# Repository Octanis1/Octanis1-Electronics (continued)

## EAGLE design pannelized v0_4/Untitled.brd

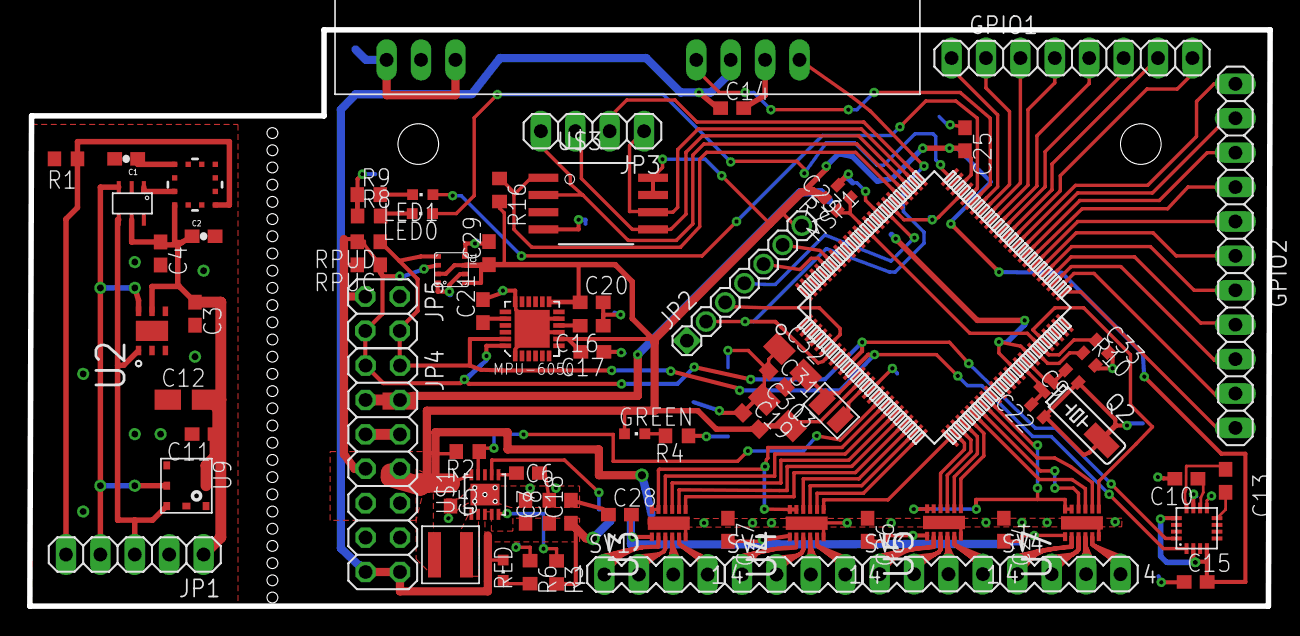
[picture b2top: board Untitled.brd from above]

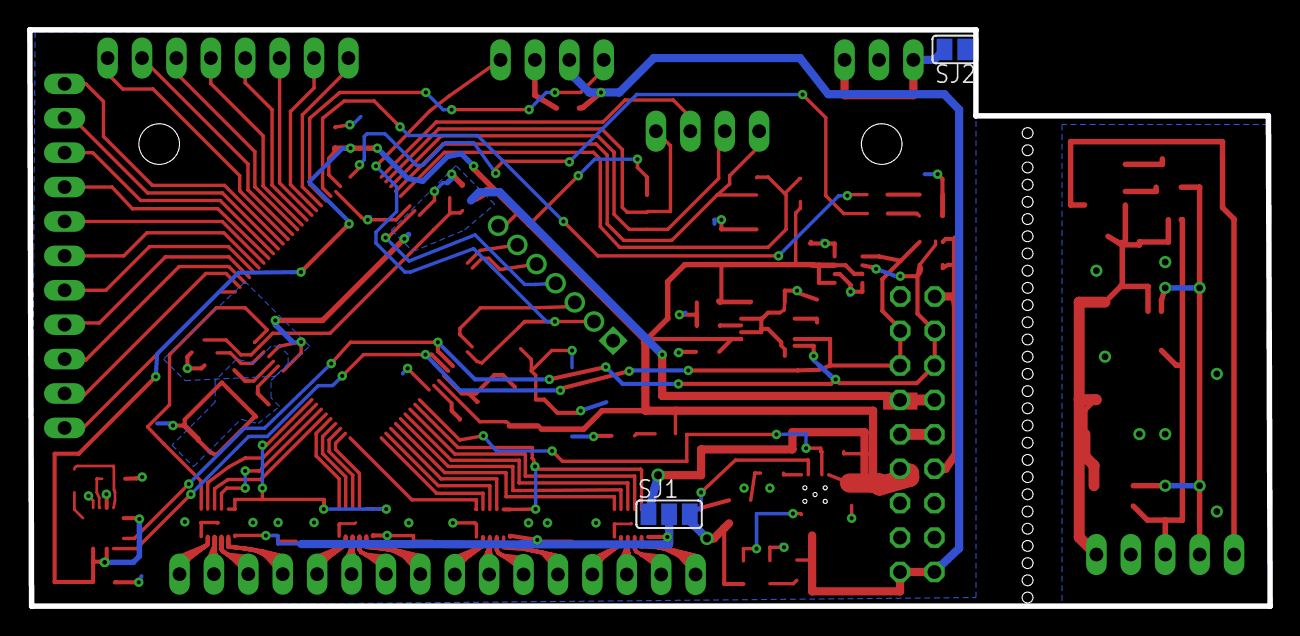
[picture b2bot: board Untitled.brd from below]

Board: 2 copper layers, 91.6 x 42.5 mm, 81 parts (2 on the bottom side), 100 nets.

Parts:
C1: 1nF; 0603-CAP
C2: 0.1uF; 0603-CAP
C3, C4, C11, C14, C15, C16, C19, C20, C25, C29, C31: 100n; C0603
C5, C7, C8: 22uF; C0603
C6: 10nF; C0603
C9, C22: 12p; C0402
C10: 4.7u; C0603
C12, C30, C32: 10u; A/3216-18R
C13: 220n; C0603
C17: 10n; C0603
C18: 3 x 22uF; C0603
C21: 2.2n; C0603
C23, C33: 100n; C0402
C24, C26, C27, C28: 470n; C0603
COMPASS: HMC5883L; LPCC16
GPIO1: A7:A0; 1X08
GPIO2: A18:A8; 1X11
GREEN: 3V-ok; CHIPLED_0603
IC1: BME280
JP1: 1X05
JP2: 1:07X2MM
JP3: SPI; 1X04
JP4: 2X07
JP5: 2X02
L1: 1uH; XFL4020
L3: 4.7uH; 0806
LED0: LED0; CHIPLED_0603
LED1: LED1; CHIPLED_0603
MPU-6050: MPU-6050; QFN24
MSP1: MSP432; PZ100
Q2: 32.768kHz; MS3V-T1R
R1, R16: 10k; R0603
R2, R3: 1M; R0603
R4, R6, R8, R9: 1k; R0603
R7: 0R; R0402
R10: 91k 0.1% ±25 ppm/°C; R0402
RED: 5V-ok; CHIPLED_0603
RPUC: 10k; R0603
RPUD: 10k; R0603
SJ1: 3V3 V_Motor 5V; SJ_2
SJ2: SJ
SV1, SV2, SV3, SV4: MA04-1
U1: ML8511-UV-SENSOR; ML8511
U2: SHT21; DFN300X300X110-7N
U3, U4, U5, U7: DRV8836DSSR; SON50P200X300X80-13N
U9: BMP180
U$1: TPS61232; S-PVSON-N10
U$2: STARGND; STAR
U$3: SST25VF064C; SOIC_8-LEAD
U$4: HX1
U$5: MCP3425; SOT-23-6

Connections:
5VEN: MSP1.17, R2.1, U$1.9
+3V1: C5.1, C15.2, C17.2, C19.2, C20.1, C25.2, C29.1, C30.+, COMPASS.2, COMPASS.4, COMPASS.13, GREEN.A, IC1.2, IC1.6, IC1.8, JP2.7, JP4.7, JP4.8, JP4.9, JP4.10, JP5.1, L1.P$1, MPU-6050.8, MPU-6050.13, MSP1.13, MSP1.73, R2.2, R7.2, R16.2, RPUC.2, RPUD.2, SJ1.1, U$1.10, U$3.RST/HOLD, U$3.VDD
+3V3: C2.1, C3.1, C4.1, C11.1, C12.+, JP1.1, U1.7, U2.5, U9.2, U9.3, U$5.VDD
+5V: C7.1, C8.1, C14.1, C18.1, JP4.13, JP4.14, R3.2, RED.A, SJ1.3, U$1.3, U$1.4, U$1.7, U$4.VCC
A14: GPIO2.7, MSP1.55
A15: GPIO2.8, MSP1.54
A16: GPIO2.9, MSP1.53
A17: GPIO2.10, MSP1.52
A18: GPIO2.11, MSP1.51
AGND: C23.2, C33.2, MSP1.40, MSP1.43, MSP1.84, R10.2, U$2.AGND
AVCC1: C23.1, C33.1, MSP1.45, MSP1.87, R7.1
GND: C1.2, C2.2, C3.2, C4.2, C11.2, C12.-, JP1.2, R1.2, U1.5, U2.2, U9.7, U$5.VIN-, U$5.VSS
GND1: C5.2, C6.2, C7.2, C8.2, C9.1, C10.2, C14.2, C15.1, C16.1, C17.1, C18.2, C19.1, C20.2, C21.2, C22.1, C24.1, C25.1, C26.1, C27.1, C28.1, C29.2, C30.-, C31.1, C32.-, COMPASS.9, COMPASS.11, IC1.1, IC1.5, IC1.7, JP2.1, JP4.3, JP4.4, JP4.5, JP4.6, JP4.11, JP4.12, JP5.2, MPU-6050.1, MPU-6050.9, MPU-6050.11, MPU-6050.18, MPU-6050.P, MSP1.15, MSP1.72, MSP1.82, Q2.P3, R4.1, R6.1, R8.1, R9.1, SJ2.1, U3.6, U3.13, U4.6, U4.13, U5.6, U5.13, U7.6, U7.13, U$1.EXPAD, U$2.DGND, U$2.GND, U$3.VSS, U$4.0V
HX1_EN: MSP1.70, U$4.EN
IND: L1.P$2, U$1.1, U$1.2
LED0: LED0.A, MSP1.75
LED1: LED1.A, MSP1.71
M1IN1: MSP1.19, U3.10
M1IN2: MSP1.20, U3.9
M2IN1: MSP1.21, U3.8
M2IN2: MSP1.22, U3.7
M3IN1: MSP1.23, U4.10
M3IN2: MSP1.24, U4.9
M4IN1: MSP1.25, U4.8
M4IN2: MSP1.26, U4.7
M5IN1: MSP1.27, U5.10
M5IN2: MSP1.28, U5.9
M6IN1: MSP1.29, U5.8
M6IN2: MSP1.30, U5.7
M7IN1: MSP1.32, U7.10
M7IN2: MSP1.31, U7.9
M8IN1: MSP1.33, U7.8
M8IN2: MSP1.46, U7.7
M1234SLEEP: MSP1.18, U3.11, U3.12, U4.11, U4.12
M5678SLEEP: MSP1.34, U5.11, U5.12, U7.11, U7.12
unnamed: U1.8, U$5.VIN+
unnamed: R3.1, U$1.5
unnamed: C1.1, U1.10
unnamed: GREEN.C, R4.2
unnamed: LED0.C, R8.2
unnamed: LED1.C, R9.2
unnamed: C31.2, C32.+, L3.1, MSP1.12
unnamed: C22.2, MSP1.41, Q2.P2
unnamed: C9.2, MSP1.42, Q2.P1
unnamed: SV2.1, U4.2
unnamed: GPIO2.1, MSP1.61
unnamed: GPIO2.2, MSP1.60
unnamed: C10.1, COMPASS.10
unnamed: C16.2, MPU-6050.10
unnamed: C21.1, MPU-6050.20
unnamed: GPIO2.3, MSP1.59
unnamed: GPIO2.4, MSP1.58
unnamed: GPIO2.5, MSP1.57
unnamed: GPIO2.6, MSP1.56
unnamed: C13.2, COMPASS.8
unnamed: GPIO1.1, MSP1.69
unnamed: GPIO1.2, MSP1.68
unnamed: GPIO1.3, MSP1.67
unnamed: C13.1, COMPASS.12
unnamed: MSP1.44, R10.1
unnamed: L3.2, MSP1.14
unnamed: GPIO1.4, MSP1.66
unnamed: GPIO1.5, MSP1.65
unnamed: GPIO1.6, MSP1.64
unnamed: GPIO1.8, MSP1.62
unnamed: SV2.2, U4.3
unnamed: SV2.3, U4.4
unnamed: SV2.4, U4.5
unnamed: C6.1, U$1.6
unnamed: GPIO1.7, MSP1.63
unnamed: R6.2, RED.C
unnamed: SV3.1, U5.2
unnamed: SV3.2, U5.3
unnamed: SV3.3, U5.4
unnamed: SV3.4, U5.5
unnamed: SV1.1, U3.2
unnamed: SV1.2, U3.3
unnamed: SV1.3, U3.4
unnamed: SV1.4, U3.5
unnamed: SV4.1, U7.2
unnamed: SV4.2, U7.3
unnamed: SV4.3, U7.4
unnamed: SV4.4, U7.5
unnamed: JP2.4, MSP1.83
unnamed: JP2.6, MSP1.94
unnamed: JP2.5, MSP1.95
RFGND: SJ2.2, U$4.RFGND, U$4.RFGND2
RX: JP2.2, MSP1.6
SCL: JP1.4, U2.6, U9.5, U$5.SCL
SCL1: COMPASS.1, IC1.4, JP4.2, JP5.4, MPU-6050.23, MSP1.11, RPUD.1
SDA: JP1.3, U2.1, U9.6, U$5.SDA
SDA1: COMPASS.16, IC1.3, JP4.1, JP5.3, MPU-6050.24, MSP1.10, RPUC.1
SPI_EXTSLAVE_TE: JP3.2, MSP1.76
SPI_FLASH_CS: MSP1.80, R16.1, U$3.CE
SPI_MISO: JP3.4, MSP1.79, U$3.SO
SPI_MOSI: JP3.3, MSP1.78, U$3.SI
SPI_SCK: JP3.1, MSP1.77, U$3.SCK
TX: JP2.3, MSP1.7, U$4.TXD
UV_EN: JP1.5, R1.1, U1.4
V_MOTOR: C24.2, C26.2, C27.2, C28.2, SJ1.2, U3.1, U4.1, U5.1, U7.1

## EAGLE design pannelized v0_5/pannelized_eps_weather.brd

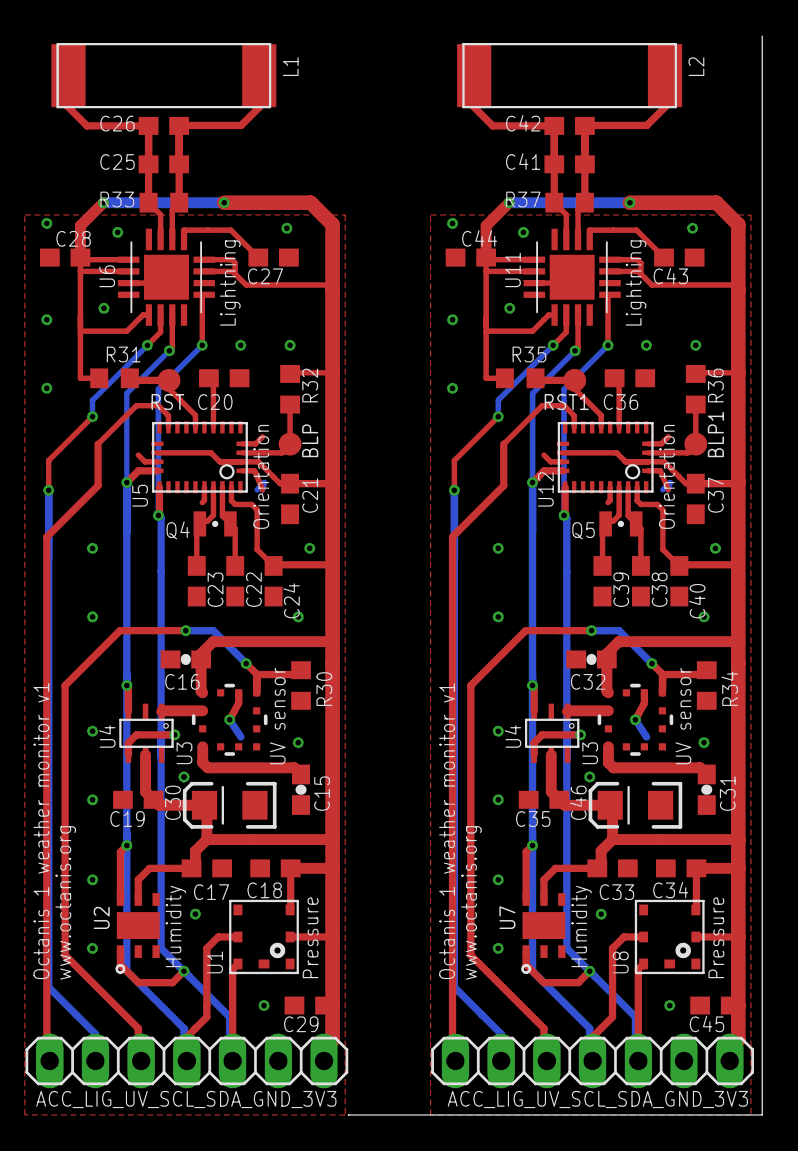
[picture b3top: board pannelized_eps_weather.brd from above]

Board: 4 copper layers, 62 parts (0 on the bottom side), 32 nets.

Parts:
BLP, BLP1: PTR1B1,27; B1,27
C15, C31: 1n; 0603-CAP
C16, C32: 100n; 0603-CAP
C17, C18, C19, C20, C21, C29, C33, C34, C35, C36, C37, C45: 100n; C0603
C22, C23, C38, C39: 12p; C0603
C24, C40: 120n; C0603
C25, C41: 670p; C0603
C26, C42: 270p; C0603
C27, C43: 10u; C0603
C28, C44: 1u; C0603
C30, C46: 10uF; EIA3216
JP4, JP5: 1X07
L1, L2: 100uH; COILCRAFT
Q4, Q5: 32.768kHz; FC-12M
R30, R31, R32, R33, R34, R35, R36, R37: 10k; R0603
RST, RST1: PTR1B1,27; B1,27
U1, U8: BMP180
U2, U7: SHT21; DFN300X300X110-7N
U3, U10: ML8511-UV-SENSORSMD; ML8511
U4, U9: MCP3425; SOT-23-6
U5, U12: BNO055A; BNO055
U6, U11: AS3935; 16LDMLPQ

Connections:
+3V1: C32.1, C33.1, C34.1, C35.1, C37.1, C40.1, C44.2, C45.1, C46.A, JP5.1, R35.1, R36.2, U7.5, U8.2, U8.3, U9.VDD, U10.7, U11.5, U11.6, U11.9, U11.15, U11.16, U12.3, U12.17, U12.28
+3V3: C16.1, C17.1, C18.1, C19.1, C21.1, C24.1, C28.2, C29.1, C30.A, JP4.1, R31.1, R32.2, U1.2, U1.3, U2.5, U3.7, U4.VDD, U5.3, U5.17, U5.28, U6.5, U6.6, U6.9, U6.15, U6.16
ACCEL_IRQ: JP4.7, U5.14
ACCEL_IRQ1: JP5.7, U12.14
ACCEL_N_BOOTLD: BLP.TP, R32.1, U5.4
ACCEL_N_BOOTLD1: BLP1.TP, R36.1, U12.4
ACCEL_N_RST: R31.2, RST.TP, U5.11
ACCEL_N_RST1: R35.2, RST1.TP, U12.11
GND1: C15.2, C16.2, C17.2, C18.2, C19.2, C20.1, C21.2, C22.2, C23.2, C24.2, C25.2, C26.2, C27.1, C28.1, C29.2, C30.C, JP4.2, L1.2, R30.2, R33.1, U1.7, U2.2, U3.5, U4.VIN-, U4.VSS, U5.2, U5.5, U5.6, U5.10, U5.15, U5.16, U5.18, U5.25, U6.2, U6.4, U6.7, U6.EXP
GND2: C31.2, C32.2, C33.2, C34.2, C35.2, C36.1, C37.2, C38.2, C39.2, C40.2, C41.2, C42.2, C43.1, C44.1, C45.2, C46.C, JP5.2, L2.2, R34.2, R37.1, U7.2, U8.7, U9.VIN-, U9.VSS, U10.5, U11.2, U11.4, U11.7, U11.EXP, U12.2, U12.5, U12.6, U12.10, U12.15, U12.16, U12.18, U12.25
LIGHTNING_IRQ: JP4.6, U6.10
LIGHTNING_IRQ1: JP5.6, U11.10
unnamed: C15.1, U3.10
unnamed: U3.8, U4.VIN+
unnamed: C25.1, C26.1, L1.1, R33.2, U6.3
unnamed: C27.2, U6.1
unnamed: C20.2, U5.9
unnamed: C22.1, Q4.2, U5.27
unnamed: C31.1, U10.10
unnamed: U9.VIN+, U10.8
unnamed: C41.1, C42.1, L2.1, R37.2, U11.3
unnamed: C43.2, U11.1
unnamed: C36.2, U12.9
unnamed: C39.1, Q5.1, U12.26
unnamed: C38.1, Q5.2, U12.27
unnamed: C23.1, Q4.1, U5.26
SCL: JP4.4, U1.5, U2.6, U4.SCL, U5.19, U6.11
SCL1: JP5.4, U7.6, U8.5, U9.SCL, U11.11, U12.19
SDA: JP4.3, U1.6, U2.1, U4.SDA, U5.20, U6.13
SDA1: JP5.3, U7.1, U8.6, U9.SDA, U11.13, U12.20
UV_EN: JP4.5, R30.1, U3.4
UV_EN1: JP5.5, R34.1, U10.4

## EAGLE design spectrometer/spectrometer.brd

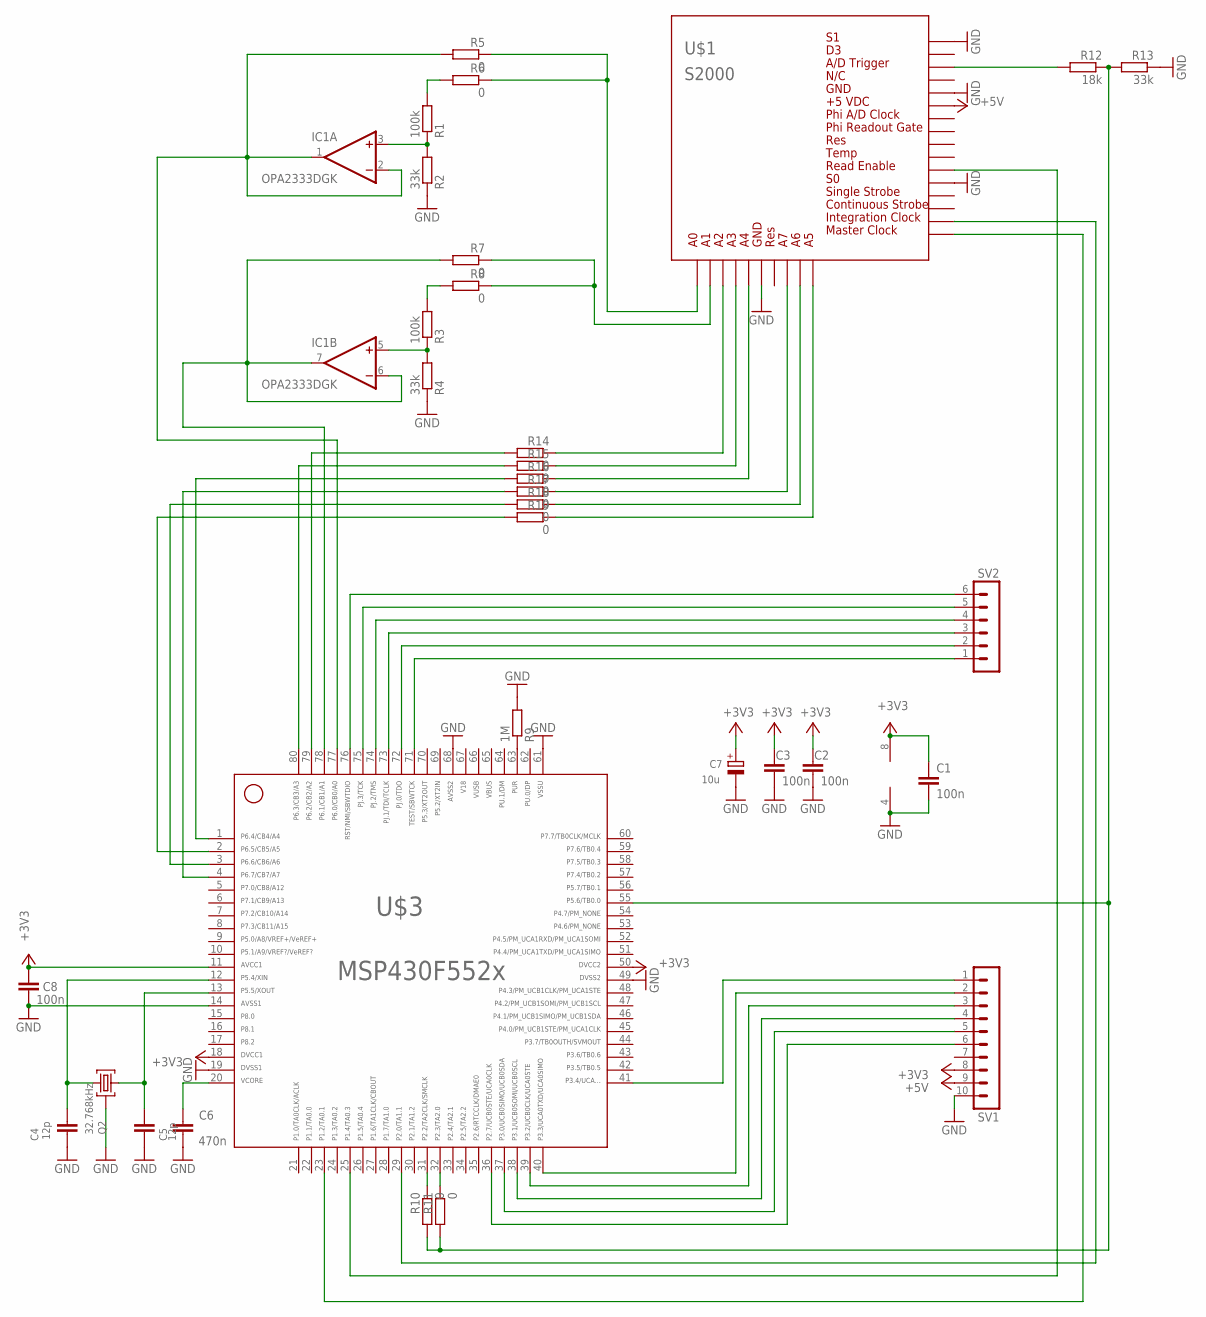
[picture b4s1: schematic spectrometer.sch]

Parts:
C1, C2, C3, C8: 100n; C0603
C4, C5: 12p; C0603
C6: 470n; C0603
C7: 10u; A/3216-18R
IC1: OPA2333DGK; MSOP08
Q2: 32.768kHz; MS3V-T1R
R1, R3: 100k; R0603
R2, R4, R13: 33k; R0603
R5, R6, R7, R8, R10, R11, R14, R15, R16, R17, R18, R19: 0; R0603
R9: 1M; R0603
R12: 18k; R0603
SV1: MA10-1
SV2: MA06-1
U$1: S2000
U$3: F552X---PN80; PN80

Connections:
65: U$3.65
66: U$3.66
67: U$3.67
+3V3: C1.1, C2.2, C3.2, C7.+, C8.1, IC1.8 (V+), SV1.8, U$3.11, U$3.18, U$3.50
+5V: SV1.9, U$1.H2$2
GND: C1.2, C2.1, C3.1, C4.1, C5.1, C6.1, C7.-, C8.2, IC1.4 (V-), Q2.P3 (GND), R2.1, R4.1, R9.2, R13.1, SV1.10, U$1.H1$6, U$1.H2$1, U$1.H2$8, U$1.H2$A, U$3.14, U$3.19, U$3.49, U$3.61, U$3.68
unnamed: IC1.3 (+IN), R1.1, R2.2
unnamed: IC1.5 (+IN), R3.1, R4.2
unnamed: IC1.1 (OUT), IC1.2 (-IN), R5.2, U$3.77
unnamed: IC1.6 (-IN), IC1.7 (OUT), R7.2, U$3.78
unnamed: R1.2, R6.2
unnamed: R3.2, R8.2
unnamed: R5.1, R6.1, U$1.H1$1
unnamed: R7.1, R8.1, U$1.H1$2
unnamed: SV1.1, U$3.41
unnamed: SV1.2, U$3.40
unnamed: SV1.3, U$3.39
unnamed: SV1.4, U$3.38
unnamed: SV1.5, U$3.37
unnamed: SV1.6, U$3.36
unnamed: R14.2, U$3.79
unnamed: R15.2, U$3.80
unnamed: R16.2, U$3.1
unnamed: R17.2, U$3.4
unnamed: R18.2, U$3.3
unnamed: R19.2, U$3.2
unnamed: R9.1, U$3.63
unnamed: SV2.1, U$3.71
unnamed: SV2.2, U$3.72
unnamed: SV2.3, U$3.73
unnamed: SV2.4, U$3.74
unnamed: SV2.5, U$3.75
unnamed: SV2.6, U$3.76
unnamed: U$1.H2$12, U$3.23
unnamed: C4.2, Q2.P2 (2), U$3.12
unnamed: C6.2, U$3.20
unnamed: C5.2, Q2.P1 (1), U$3.13
unnamed: U$1.H2$11, U$3.29
unnamed: R10.1, U$3.31
unnamed: R11.1, U$3.32
unnamed: R10.2, R11.2, R12.1, R13.2, U$3.55
unnamed: R14.1, U$1.H1$3
unnamed: R12.2, U$1.H2$C
unnamed: R15.1, U$1.H1$4
unnamed: R16.1, U$1.H1$5
unnamed: R17.1, U$1.H1$8
unnamed: R18.1, U$1.H1$9
unnamed: U$1.H2$7, U$3.25
unnamed: R19.1, U$1.H1$10

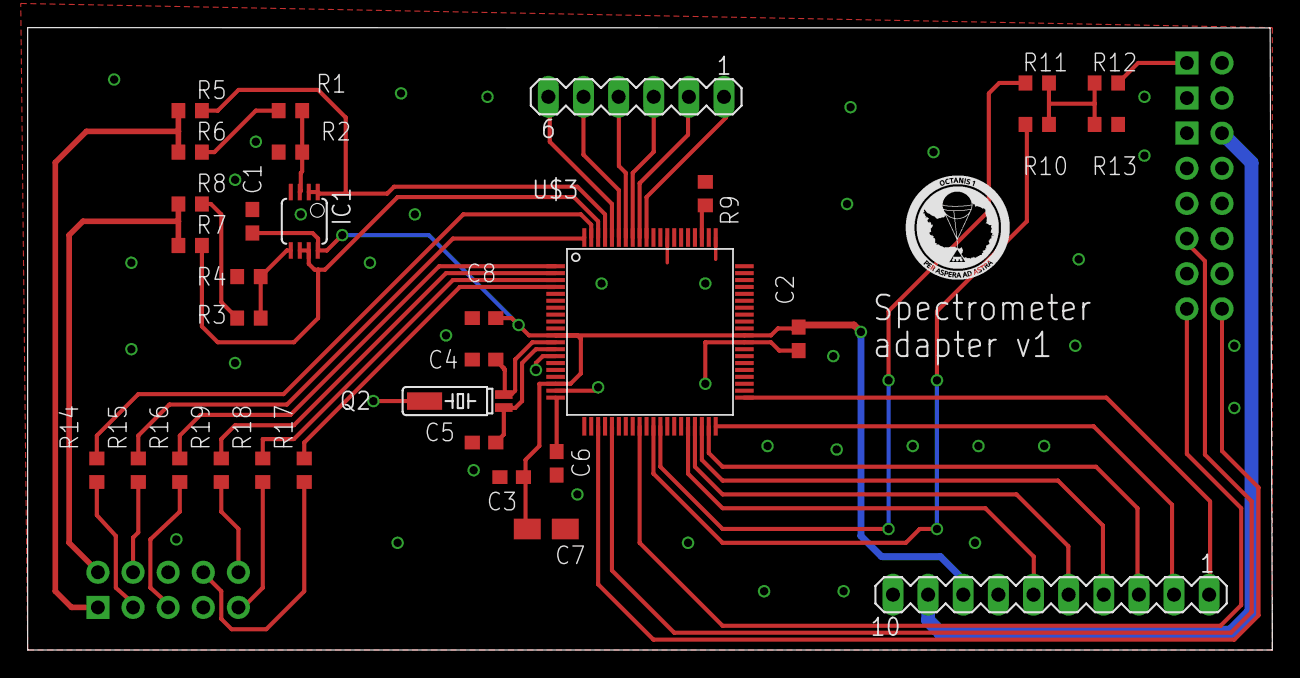
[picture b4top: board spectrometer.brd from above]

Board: 2 copper layers, 90.0 x 45.0 mm, 33 parts (0 on the bottom side), 46 nets.
